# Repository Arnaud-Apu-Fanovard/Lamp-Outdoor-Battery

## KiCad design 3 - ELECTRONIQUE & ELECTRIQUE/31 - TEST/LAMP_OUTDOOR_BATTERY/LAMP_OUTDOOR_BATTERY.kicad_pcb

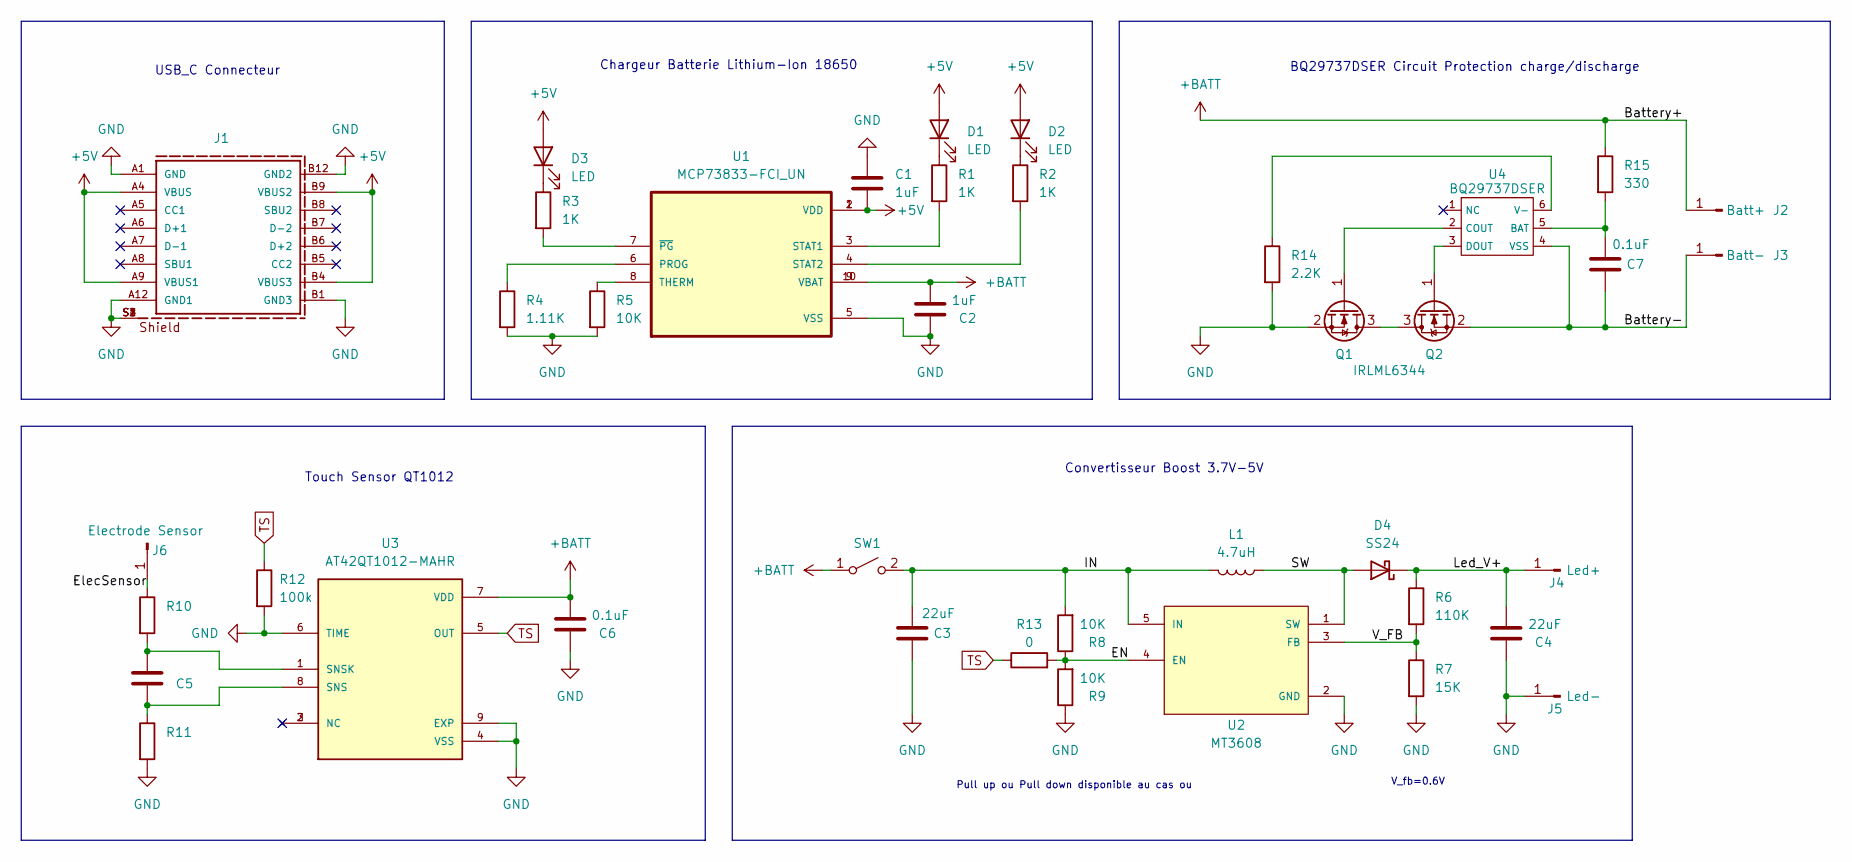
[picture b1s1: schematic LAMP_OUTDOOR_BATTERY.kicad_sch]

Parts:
C1, C2: 1uF; C_0402_1005Metric_Pad0.74x0.62mm_HandSolder
C3, C4: 22uF; C_0402_1005Metric_Pad0.74x0.62mm_HandSolder
C5: C_0402_1005Metric_Pad0.74x0.62mm_HandSolder
C6, C7: 0.1uF; C_0402_1005Metric_Pad0.74x0.62mm_HandSolder
D1, D2, D3: LED; LED_0805_2012Metric_Pad1.15x1.40mm_HandSolder
D4: SS24; D_SMA
J1: 629722000214; USB-C Connecteur 16p; PART-NUMBER 629722000214
J2: Batt+; BatteryPole
J3: Batt-; BatteryPole
J4: Led+; BatteryPole
J5: Led-; BatteryPole
J6: Electrode Sensor; BatteryPole
L1: 4.7uH; IND_F1C1-201608-4R7M
Q1, Q2: IRLML6344; SOT-23-3
R1, R2, R3: 1K; R_0402_1005Metric_Pad0.72x0.64mm_HandSolder
R4: 1.11K; R_0402_1005Metric_Pad0.72x0.64mm_HandSolder
R5, R8, R9: 10K; R_0402_1005Metric_Pad0.72x0.64mm_HandSolder
R6: 110K; R_0402_1005Metric_Pad0.72x0.64mm_HandSolder
R7: 15K; R_0402_1005Metric_Pad0.72x0.64mm_HandSolder
R10, R11: R_0402_1005Metric_Pad0.72x0.64mm_HandSolder
R12: 100k; R_0402_1005Metric_Pad0.72x0.64mm_HandSolder
R13: 0; R_0402_1005Metric_Pad0.72x0.64mm_HandSolder
R14: 2.2K; R_0402_1005Metric_Pad0.72x0.64mm_HandSolder
R15: 330; R_0402_1005Metric_Pad0.72x0.64mm_HandSolder
SW1: SW_SPST; PinHeader_1x02_P2.54mm_Vertical
U1: MCP73833-FCI_UN; MCP73833
U2: MT3608; MT3608_SOT95P280X145-6N; PARTREV 1.0
U3: AT42QT1012-MAHR; SON50P200X200X60-9N; PARTREV I
U4: BQ29737DSER; WSON-6_1.5x1.5mm_P0.5mm

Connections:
+5V: C1.2, D1.2 (A), D2.2 (A), D3.2 (A), J1.A4 (VBUS), J1.A9 (VBUS1), J1.B4 (VBUS3), J1.B9 (VBUS2), U1.1 (VDD), U1.2 (VDD)
+BATT: C2.2, C6.2, J2.1, R15.1, SW1.1 (A), U1.9 (VBAT), U1.10 (VBAT), U3.7 (VDD)
/Battery-: C7.1, J3.1, Q2.2 (S), U4.4 (VSS)
/EN: R8.1, R9.2, R13.2, U2.4 (EN)
/ElecSensor: J6.1, R10.1
/IN: C3.2, L1.2, R8.2, SW1.2 (B), U2.5 (IN)
/Led_V+: C4.2, D4.1 (K), J4.1, R6.1
/SW: D4.2 (A), L1.1, U2.1 (SW)
/V_FB: R6.2, R7.1, U2.3 (FB)
GND: C1.1, C2.1, C3.1, C4.1, C6.1, J1.A1 (GND), J1.A12 (GND1), J1.B1 (GND3), J1.B12 (GND2), J1.S1, J1.S2, J1.S3, J1.S4, J5.1, Q1.2 (S), R4.2, R5.2, R7.2, R9.1, R11.2, R12.2, R14.2, U1.5 (VSS), U2.2 (GND), U3.4 (VSS), U3.6 (TIME), U3.9 (EXP)
unnamed: D1.1 (K), R1.1
unnamed: D2.1 (K), R2.1
unnamed: D3.1 (K), R3.1
unnamed: Q1.3 (D), Q2.3 (D)
unnamed: Q1.1 (G), U4.2 (COUT)
unnamed: Q2.1 (G), U4.3 (DOUT)
unnamed: R4.1, U1.6 (PROG)
unnamed: R1.2, U1.3 (STAT1)
unnamed: R2.2, U1.4 (STAT2)
unnamed: R5.1, U1.8 (THERM)
unnamed: R3.2, U1.7 (~PG)
unnamed: C5.1, R11.1, U3.8 (SNS)
unnamed: C5.2, R10.2, U3.1 (SNSK)
unnamed: C7.2, R15.2, U4.5 (BAT)
unnamed: R14.1, U4.6 (V-)
TS: R12.1, R13.1, U3.5 (OUT)

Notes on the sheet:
Convertisseur Boost 3.7V-5V
BQ29737DSER Circuit Protection charge/discharge
USB_C Connecteur
Touch Sensor QT1012
Pull up ou Pull down disponible au cas ou
Chargeur Batterie Lithium-Ion 18650
V_fb=0.6V

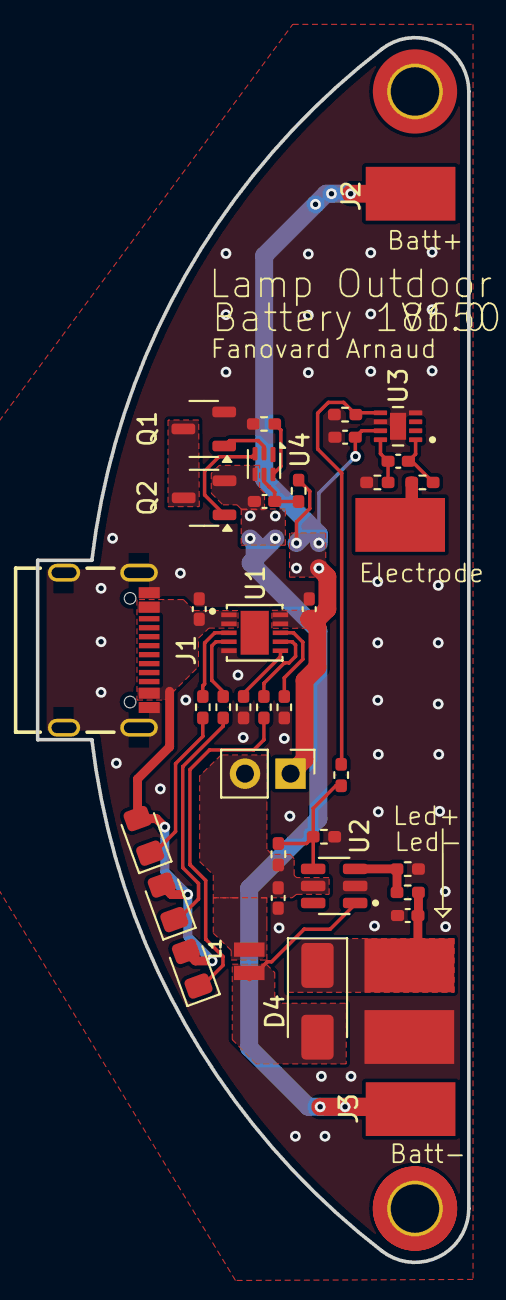
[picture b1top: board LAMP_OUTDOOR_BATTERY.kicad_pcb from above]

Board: 2 copper layers, 24.0 x 68.3 mm, 40 parts (0 on the bottom side), 26 nets.

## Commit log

2025-01-17 Commit_0.0 Creation of folders
    Project initialization
2025-01-20 Commit_1.0 Conception théorique
2025-01-20 Commit_1.01 Test impression socle
2025-01-21 Commit_1.02 Modification shape PCB
2025-01-23 Commit_1.03 Conception 3D
2025-01-23 Boost converter circuit
2025-01-23 Import des symboles et empreintes
2025-01-28 Conception schéma suite
2025-01-29 Conception PCB suite
2025-01-30 PCB & Conception 3D V1
2025-01-30 Impression 3D Socle
2025-02-05 Schéma pdf et backup
2025-02-19 Commande composants
